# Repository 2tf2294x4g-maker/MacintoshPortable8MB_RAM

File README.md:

# Mac Portable 8MB RAM Card (v2 — All-5V)

Expands a Macintosh Portable to **9 MB total** (1 MB onboard + 8 MB this card) — the maximum the Portable's address space supports.

All-5V design using 1M×8 SRAM chips. No level shifters, no LDO regulator, no 3.3V rail. Shares the same connector, CPLD, and bus transceiver approach as the [4MB card](https://github.com/2tf2294x4g-maker/MacintoshPortable4MB_RAM) but doubles capacity using larger SRAM.

> ✅ **HARDWARE VALIDATED** — Built and tested on a Mac Portable M5120 (July 2026). Boots reliably, passes 9 MB in About This Macintosh, and with the DTACK bodge (see below) outperforms the 1 MB baseline.

---

## Photos

| | |
|---|---|
|  |  |
| System 7.5.5 — 9,216K total memory | Card seated in Portable with orange DTACK bodge wire |

*Orange bodge wire running from CPLD pin 42 to PDS slot pin B7 (/DTACK)*

| | |
|---|---|
|  |  |
| Component side — all 8 AS6C8008 SRAMs, bus transceivers, CPLD, and DTACK bodge wire | Solder side — bypass caps and bulk caps

---

## Specs

| | |
|---|---|
| Capacity | 8 MB (8× 1M×8 SRAM) |
| System total | 9 MB (1 MB onboard + 8 MB card) |
| Bus width | 8-bit × 2 banks (addressed via CPLD) |
| Logic | ATF1502ASL CPLD (5V, TQFP-44) |
| SRAM | 8× AS6C8008-55ZIN (5V, TSOP-II-44) |
| Layers | 4 (F.Cu signal / GND plane / +5V plane / B.Cu signal + pour) |
| Connector | Samtec BCS-125-F-D-HE (50-pin 2×25, horizontal entry) |
| Size jumper | JP1: OPEN = 8MB (all chips) / CLOSED = 4MB (populate U2 U3 U6 U7 only) |

---

## Bill of Materials

| Ref | Qty | Value | Package | Part / Notes |
|-----|----:|-------|---------|--------------|
| U2–U9 | 8 | AS6C8008-55ZIN | TSOP-II-44 | Alliance Memory — 1M×8 5V SRAM 55 ns |
| U1 | 1 | ATF1502ASL | TQFP-44 | Microchip ATF1502ASL-**25AU44** — must be ASL (5V), not ASV |
| U11, U12 | 2 | 74HC245 | SOIC-20 **wide** | SN74HC245**DW** — verify wide (7.5 mm) body |
| J1 | 1 | RAM connector | Samtec BCS-125-F-D-HE | 50-pin socket, horizontal entry — free Samtec sample |
| J2 | 1 | JTAG header | 1×6 2.54 mm pin header | Pin 1 (square pad) = TCK |
| JP1 | 1 | SIZE jumper | 1×2 2.54 mm pin header + shunt | OPEN=8MB, CLOSED=4MB |
| C1–C12, C17, C18 | 14 | 100 nF | 0805 | X7R 50V ceramic bypass |
| C13–C16, C19 | 5 | 10 µF | 0805 | X5R 16V ceramic bulk |
| R2–R5 | 4 | 10 KΩ | 0805 | 5% thick film |

Full BOM: [PortableRAM-8MB-BOM.csv](PortableRAM-8MB-BOM.csv)

---

## ⚠️ Important — SRAM Pinout Difference

The AS6C8008 (8MB card) and AS7C4096A (4MB card) are **both TSOP-II-44 but have different pinouts**. Do not install 4MB card SRAM chips on this board — the CE#, WE#, and OE# pins are in different locations and the board will not work correctly.

---

## Population Guide

The silkscreen shows two labeled boxes:

| Box | Chips | Config |
|-----|-------|--------|
| **4MB** | U2, U3, U6, U7 | JP1 CLOSED — populate these 4 chips only |
| **8MB ONLY** | U4, U5, U8, U9 | JP1 OPEN — populate all 8 chips |

For a full 8MB build, populate all 8 chips and leave JP1 open (no shunt).

---

## Files

```
PortableRAM-8MB.kicad_pcb     — PCB layout (KiCad 9)
PortableRAM-8MB.kicad_sch     — Schematic
PortableRAM-8MB.kicad_pro     — Project file
PortableRAM.kicad_sym         — Custom symbol library
PortableRAM.pretty/           — Custom footprint library
Gerbers/                      — Gerber + drill files (ready to order)
Gerbers.zip                   — Same, zipped (upload directly to fab)
firmware/
  PortableRAM8.pld            — CUPL source (ATF1502ASL logic)
  PortableRAM8.jed            — Compiled JEDEC
  PortableRAM8.svf            — SVF for OpenOCD programming
  program.sh                  — One-command programming script (Tigard)
  BUILD.md                    — Firmware build instructions (WinCUPL + Wine)
PortableRAM-8MB-BOM.csv
```

---

## Ordering the PCB

Upload `Gerbers.zip` to your preferred fab (JLCPCB, PCBWay, OSHPark, etc.).

**Board settings:**
- Layers: **4**
- Thickness: 1.6 mm
- Surface finish: **ENIG** (recommended — 0.8mm pitch fine-pitch pads benefit from the flat surface)
- All other settings: fab defaults

---

## Assembly Notes

Solder in this order:

1. **U1** (ATF1502ASL CPLD, TQFP-44) — centre first
2. **U2–U9** (SRAM, TSOP-II-44) — fine pitch; flux generously. See population guide above.
3. **U11, U12** (74HC245, SOIC-20 wide)
4. **C1–C18** (100 nF 0805 bypass caps)
5. **C13–C19** (10 µF 0805 bulk caps)
6. **R2–R5** (10 KΩ 0805)
7. **JP1** (1×2 header — leave open for 8MB, or install shunt for 4MB)
8. **J2** (1×6 JTAG header — before J1 for iron clearance)
9. **J1** (Samtec connector) — last

---

## Programming the CPLD

The ATF1502ASL must be programmed before the card will work. Use J2 (1×6 header on the board edge).

### J2 pinout (pin 1 = square pad)

| Pin | Signal |
|-----|--------|
| 1 | TCK |
| 2 | TMS |
| 3 | TDI |
| 4 | TDO |
| 5 | +5V |
| 6 | GND |

### With a Tigard programmer (FT2232H-based)

Set the Tigard voltage jumper to **5V** before connecting.

```bash
cd firmware
./program.sh PortableRAM8.svf
```

Success output ends with `shutdown command invoked` and no TDO mismatch errors.

See [firmware/BUILD.md](firmware/BUILD.md) for full build and programming pipeline.

---

## Installation

1. Power off and unplug the Mac Portable.
2. Remove the battery and bottom cover.
3. Seat the card on the RAM expansion header — J1 is a friction-fit horizontal-entry socket.
4. Reassemble and power on.

You should see **9 MB** in About This Macintosh.

### DTACK Performance Fix (firmware rev 12)

The Mac Portable's GLU chip generates /DTACK for the 68000 with region-dependent timing:

| Address range | GLU /DTACK | Condition |
|---|---|---|
| 0x000000–0x4FFFFF | 2 clocks | Always — hardwired fast path |
| 0x500000–0x8FFFFF | 6 clocks | Normal operation (register configured) |
| 0x500000–0x8FFFFF | 18 clocks | After sleep/wake (register reset) |

The 8 MB card spans 0x100000–0x8FFFFF, straddling the split. Banks 0–1 (0x100000–0x4FFFFF) already get the GLU's 2-clock fast path. Banks 2–3 (0x500000–0x8FFFFF) run at 6 clocks and collapse to 18 clocks after sleep/wake when the GLU's DTACK register loses its configuration.

The fix: the ATF1502ASL CPLD now asserts /DTACK itself, via a bodge wire from CPLD pin 42 to PDS slot pin B7. The CPLD monitors the address bus and data strobes, and whenever a cycle falls within the card's memory window (0x100000–0x8FFFFF) it pulls /DTACK low directly — bypassing the GLU completely. The output is tristated for all other bus cycles so there's no contention.

Because the logic is purely combinatorial (no registers, no state), it's immune to sleep/wake — the CPLD re-evaluates every cycle from scratch. The post-sleep collapse is gone.

**Benchmark results (Speedometer 3.23 / Snooper Memory Move — System 7.1, M5120):**

| Configuration | Speedometer | Snooper | Post-sleep |
|---|---|---|---|
| 1 MB card (baseline) | 1.990 | 87% | 1.985 |
| 4 MB expansion card | 1.955 | 85% | — |
| 8 MB card — no DTACK bodge | 1.486 | 51% | — |
| 8 MB card — no bodge, after sleep | 0.974 | 22% | — |
| **8 MB card + CPLD DTACK bodge** | **2.170** | **102%** | **2.170** |
| **4 MB card + CPLD DTACK bodge** | **2.170** | **102%** | **2.170** |

The CPLD's combinatorial DTACK is faster than the GLU — the 8 MB card with the bodge outperforms the 1 MB baseline. Post-sleep performance is identical to cold boot. The 4 MB configuration with the DTACK bodge also scores 102%, confirming the CPLD path is faster than even the GLU's hardwired 2-clock mode for the lower address range.

**How to wire it:** Solder a bodge wire from CPLD pin 42 (U1, TQFP-44) to PDS slot pin B7 (/DTACK). The PDS connector is the 96-pin DIN-41612 on the Mac Portable motherboard (3 rows A/B/C, 32 pins each). Pin B7 is in row B, position 7 from the component side.

---

## Cost

### PCB — JLCPCB (July 2026)

| | |
|---|---|
| 5× 4-layer boards (ENIG) | $48.70 |
| Shipping | $8.79 |
| Discount | −$5.49 |
| Tax | $3.68 |
| Payment fee | $0.52 |
| **Total for 5 boards** | **$56.20** |
| **Per board** | **~$11.24** |

ENIG finish recommended over HASL for the 0.8mm pitch TSOP-II-44 and TQFP-44 pads.

### Parts — DigiKey

| Part | Qty | Unit | Ext |
|------|----:|-----:|----:|
| ATF1502ASL-25AU44 (CPLD) | 1 | $3.12 | $3.12 |
| SN74HC245DWR (74HC245 wide SOIC) | 2 | $0.75 | $1.50 |
| 100 nF 50V X7R 0805 | 14 | $0.07 | $0.98 |
| 10 µF 16V X5R 0805 | 5 | $0.46 | $2.30 |
| 10 KΩ 5% 0805 | 4 | $0.03 | $0.12 |

### Parts — DigiKey (SRAM)

| Part | Qty | Unit | Ext |
|------|----:|-----:|----:|
| AS6C8008-55ZIN (1M×8 5V SRAM) | 10 | ~$10.17 | ~$102 |

Order 10 (8 needed + 2 spares).

### Samtec J1 Connector

Free sample from samtec.com (BCS-125-F-D-HE). Allow 1–2 weeks.

### Summary — one board from scratch

| Item | Approx cost |
|---|---|
| PCB (1 of 5 from JLCPCB, ENIG) | $11 |
| 8× AS6C8008-55ZIN SRAM | $86 |
| CPLD + transceivers + passives | $8 |
| Samtec J1 | free / ~$10 |
| **Total** | **~$105–115** |

The SRAM dominates the cost. Compared to the 4MB card (~$93–103), the extra cost is the larger SRAM chips and ENIG finish.

---

## References & Acknowledgements

This card would not exist without the following prior work:

**Dynamic Engineering Mac Portable RAM Card**
The address decode and bus control logic in `PortableRAM8.pld` is derived from the GAL22V10 PLD source files originally written for the Dynamic Engineering commercial RAM expansion card for the Mac Portable. These files define the core signal equations — bank chip-select generation, byte-lane write control via UDS*/LDS*, bus transceiver direction, and output enable timing. The original `.PLD` files were recovered and shared by *techknight* on the TinkerDifferent forum and #skunkworks Discord. Translated here from three GAL22V10 chips to a single ATF1502ASL CPLD, with corrections to the `r_w_u` equation and address decode base, and extended for 8MB capacity.

**miejas — Macintosh Portable 4MB Memory Expansion**
[https://github.com/miejas/Macintosh-Portable-4-MB-Memory-Expansion](https://github.com/miejas/Macintosh-Portable-4-MB-Memory-Expansion)
Open-source 4MB RAM card whose connector pinout, bus transceiver approach, and firmware structure were used as a cross-reference to validate signal assignments and confirm that AS* and SLEEP* are not present on the expansion connector.

**Reza Fouladian — PortableRAM BGA 8MB**
[https://github.com/rezafouladian/PortableRAM-BGA-8MB](https://github.com/rezafouladian/PortableRAM-BGA-8MB)
BGA-format 8MB card using the ATF1502ASV (3.3V CPLD) and SN74LVC4245A level translators. Used as a reference for the 8MB address decode strategy and CPLD pin planning. Reza also provided direct guidance on driving /DTACK from the CPLD and on the Mac Portable PDS connector pinout — specifically confirming that /DTACK is available on PDS pin B7 and can be driven directly from a CPLD output, which was the key insight that led to the DTACK bodge fix implemented in firmware rev 12. That fix eliminated the GLU wait-state penalty and the post-sleep performance collapse entirely.

**Apple Mac Portable Developer Notes & Schematics**
Apple's original hardware documentation for the Mac Portable expansion bus, memory map, and GLU register behaviour (including the $FC0200 DTACK register).

---

## License

- **Hardware** (schematics, PCB layout, Gerbers) — [CERN-OHL-S v2](LICENSE) · SPDX `CERN-OHL-S-2.0`
- **Firmware source** (`PortableRAM8.pld`) — [MIT](LICENSE-MIT) · SPDX `MIT`

Both licence texts are included in full in this repository.
Do what you like — just share improvements.

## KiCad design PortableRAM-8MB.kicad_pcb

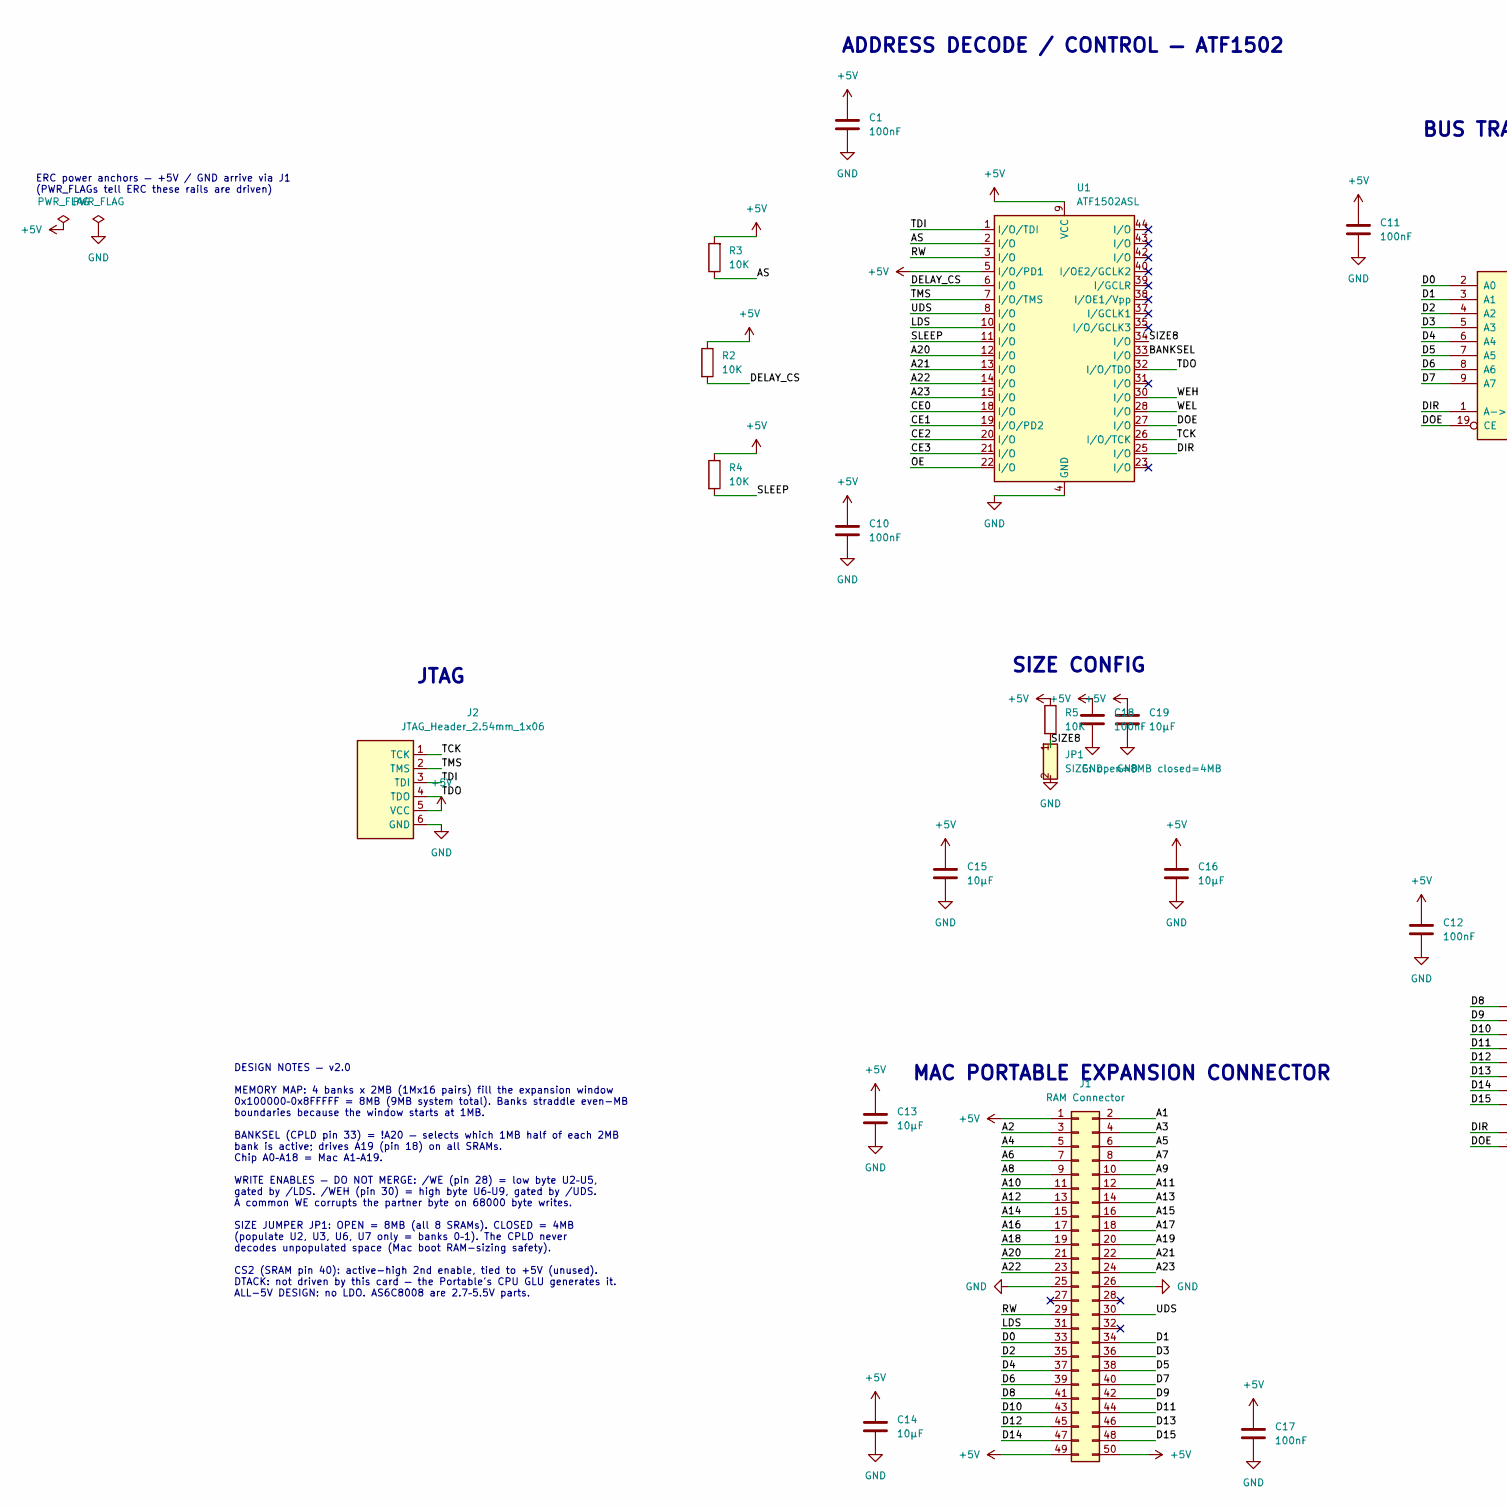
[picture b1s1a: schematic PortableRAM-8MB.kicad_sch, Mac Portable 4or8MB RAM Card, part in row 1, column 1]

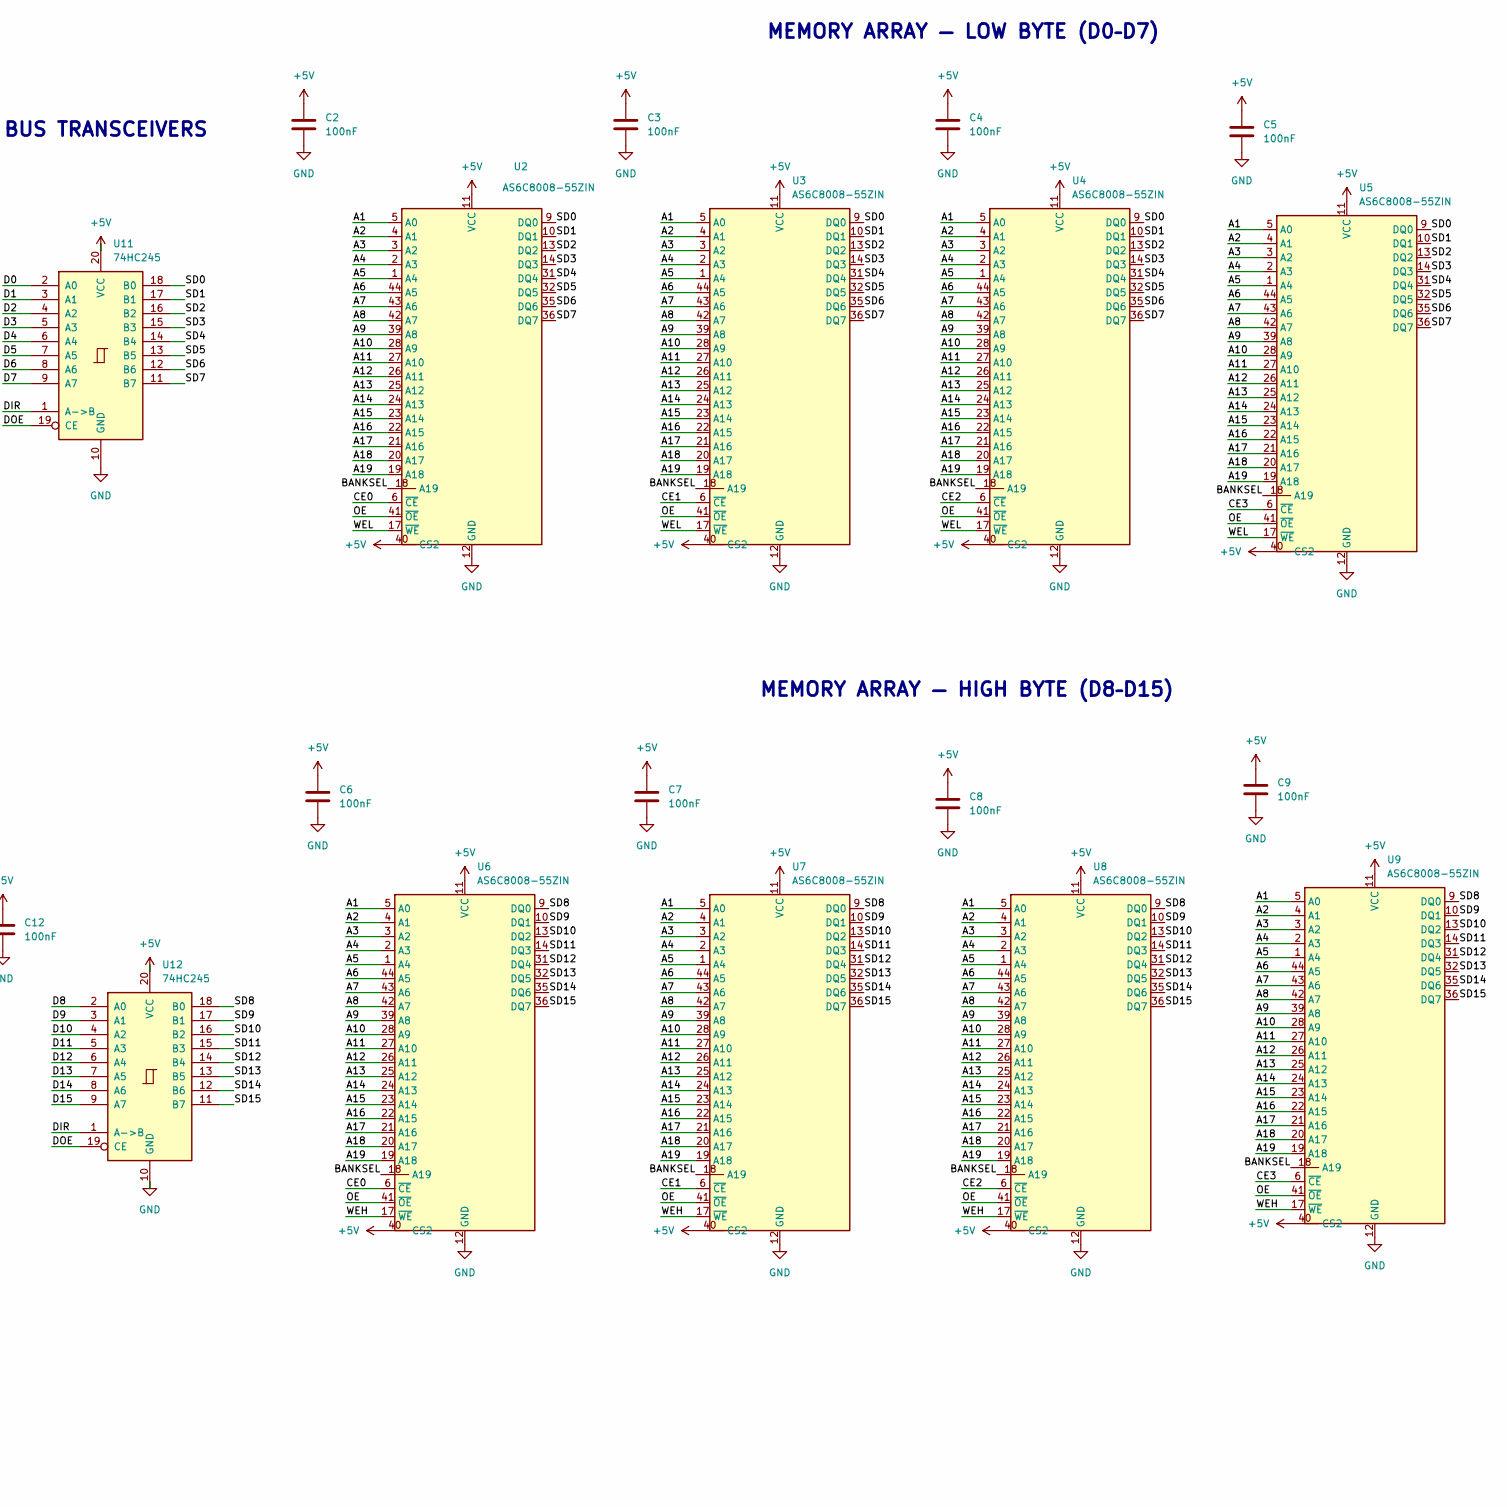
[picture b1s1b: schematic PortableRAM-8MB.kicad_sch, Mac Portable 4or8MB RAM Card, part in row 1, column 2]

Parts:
C1, C2, C3, C4, C5, C6, C7, C8, C9, C10, C11, C12, C17, C18: 100nF; C_0805_2012Metric
C13, C14, C15, C16, C19: 10µF; C_0805_2012Metric
J1: RAM Connector; Samtec_BCS-125-F-D-HE
J2: JTAG_Header_2.54mm_1x06; PinHeader_1x06_P2.54mm_Vertical
JP1: SIZE: open=8MB closed=4MB; PinHeader_1x02_P2.54mm_Vertical
R2, R3, R4, R5: 10K; R_0805_2012Metric
U1: ATF1502ASL; TQFP-44_10x10mm_P0.8mm
U2, U3, U4, U5, U6, U7, U8, U9: AS6C8008-55ZIN; TSOP-II-44_10.16x18.41mm_P0.8mm
U11, U12: 74HC245; SOIC-20W_7.5x12.8mm_P1.27mm

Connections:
+5V: C1.1, C2.1, C3.1, C4.1, C5.1, C6.1, C7.1, C8.1, C9.1, C10.1, C11.1, C12.1, C13.1, C14.1, C15.1, C16.1, C17.1, C18.1, C19.1, J1.1, J1.49, J1.50, J2.5 (VCC), R2.1, R3.2, R4.1, R5.1, U1.5 (I/O/PD1), U1.9 (VCC), U1.17 (VCC), U1.29 (VCC), U1.41 (VCC), U2.11 (VCC), U2.33 (VCC), U2.40 (CS2), U3.11 (VCC), U3.33 (VCC), U3.40 (CS2), U4.11 (VCC), U4.33 (VCC), U4.40 (CS2), U5.11 (VCC), U5.33 (VCC), U5.40 (CS2), U6.11 (VCC), U6.33 (VCC), U6.40 (CS2), U7.11 (VCC), U7.33 (VCC), U7.40 (CS2), U8.11 (VCC), U8.33 (VCC), U8.40 (CS2), U9.11 (VCC), U9.33 (VCC), U9.40 (CS2), U11.20 (VCC), U12.20 (VCC)
/A1: J1.2, U2.5 (A0), U3.5 (A0), U4.5 (A0), U5.5 (A0), U6.5 (A0), U7.5 (A0), U8.5 (A0), U9.5 (A0)
/A2: J1.3, U2.4 (A1), U3.4 (A1), U4.4 (A1), U5.4 (A1), U6.4 (A1), U7.4 (A1), U8.4 (A1), U9.4 (A1)
/A3: J1.4, U2.3 (A2), U3.3 (A2), U4.3 (A2), U5.3 (A2), U6.3 (A2), U7.3 (A2), U8.3 (A2), U9.3 (A2)
/A4: J1.5, U2.2 (A3), U3.2 (A3), U4.2 (A3), U5.2 (A3), U6.2 (A3), U7.2 (A3), U8.2 (A3), U9.2 (A3)
/A5: J1.6, U2.1 (A4), U3.1 (A4), U4.1 (A4), U5.1 (A4), U6.1 (A4), U7.1 (A4), U8.1 (A4), U9.1 (A4)
/A6: J1.7, U2.44 (A5), U3.44 (A5), U4.44 (A5), U5.44 (A5), U6.44 (A5), U7.44 (A5), U8.44 (A5), U9.44 (A5)
/A7: J1.8, U2.43 (A6), U3.43 (A6), U4.43 (A6), U5.43 (A6), U6.43 (A6), U7.43 (A6), U8.43 (A6), U9.43 (A6)
/A8: J1.9, U2.42 (A7), U3.42 (A7), U4.42 (A7), U5.42 (A7), U6.42 (A7), U7.42 (A7), U8.42 (A7), U9.42 (A7)
/A9: J1.10, U2.39 (A8), U3.39 (A8), U4.39 (A8), U5.39 (A8), U6.39 (A8), U7.39 (A8), U8.39 (A8), U9.39 (A8)
/A10: J1.11, U2.28 (A9), U3.28 (A9), U4.28 (A9), U5.28 (A9), U6.28 (A9), U7.28 (A9), U8.28 (A9), U9.28 (A9)
/A11: J1.12, U2.27 (A10), U3.27 (A10), U4.27 (A10), U5.27 (A10), U6.27 (A10), U7.27 (A10), U8.27 (A10), U9.27 (A10)
/A12: J1.13, U2.26 (A11), U3.26 (A11), U4.26 (A11), U5.26 (A11), U6.26 (A11), U7.26 (A11), U8.26 (A11), U9.26 (A11)
/A13: J1.14, U2.25 (A12), U3.25 (A12), U4.25 (A12), U5.25 (A12), U6.25 (A12), U7.25 (A12), U8.25 (A12), U9.25 (A12)
/A14: J1.15, U2.24 (A13), U3.24 (A13), U4.24 (A13), U5.24 (A13), U6.24 (A13), U7.24 (A13), U8.24 (A13), U9.24 (A13)
/A15: J1.16, U2.23 (A14), U3.23 (A14), U4.23 (A14), U5.23 (A14), U6.23 (A14), U7.23 (A14), U8.23 (A14), U9.23 (A14)
/A16: J1.17, U2.22 (A15), U3.22 (A15), U4.22 (A15), U5.22 (A15), U6.22 (A15), U7.22 (A15), U8.22 (A15), U9.22 (A15)
/A17: J1.18, U2.21 (A16), U3.21 (A16), U4.21 (A16), U5.21 (A16), U6.21 (A16), U7.21 (A16), U8.21 (A16), U9.21 (A16)
/A18: J1.19, U2.20 (A17), U3.20 (A17), U4.20 (A17), U5.20 (A17), U6.20 (A17), U7.20 (A17), U8.20 (A17), U9.20 (A17)
/A19: J1.20, U2.19 (A18), U3.19 (A18), U4.19 (A18), U5.19 (A18), U6.19 (A18), U7.19 (A18), U8.19 (A18), U9.19 (A18)
/A20: J1.21, U1.12 (I/O)
/A21: J1.22, U1.13 (I/O)
/A22: J1.23, U1.14 (I/O)
/A23: J1.24, U1.15 (I/O)
/AS: R3.1, U1.2 (I/O)
/BANKSEL: U1.33 (I/O), U2.18 (A19), U3.18 (A19), U4.18 (A19), U5.18 (A19), U6.18 (A19), U7.18 (A19), U8.18 (A19), U9.18 (A19)
/CE0: U1.18 (I/O), U2.6 (~CE), U6.6 (~CE)
/CE1: U1.19 (I/O/PD2), U3.6 (~CE), U7.6 (~CE)
/CE2: U1.20 (I/O), U4.6 (~CE), U8.6 (~CE)
/CE3: U1.21 (I/O), U5.6 (~CE), U9.6 (~CE)
/D0: J1.33, U11.2 (A0)
/D1: J1.34, U11.3 (A1)
/D2: J1.35, U11.4 (A2)
/D3: J1.36, U11.5 (A3)
/D4: J1.37, U11.6 (A4)
/D5: J1.38, U11.7 (A5)
/D6: J1.39, U11.8 (A6)
/D7: J1.40, U11.9 (A7)
/D8: J1.41, U12.2 (A0)
/D9: J1.42, U12.3 (A1)
/D10: J1.43, U12.4 (A2)
/D11: J1.44, U12.5 (A3)
/D12: J1.45, U12.6 (A4)
/D13: J1.46, U12.7 (A5)
/D14: J1.47, U12.8 (A6)
/D15: J1.48, U12.9 (A7)
/DELAY_CS: R2.2, U1.6 (I/O)
/DIR: U1.25 (I/O), U11.1 (A->B), U12.1 (A->B)
/DOE: U1.27 (I/O), U11.19 (CE), U12.19 (CE)
/LDS: J1.31, U1.10 (I/O)
/OE: U1.22 (I/O), U2.41 (~OE), U3.41 (~OE), U4.41 (~OE), U5.41 (~OE), U6.41 (~OE), U7.41 (~OE), U8.41 (~OE), U9.41 (~OE)
/RW: J1.29, U1.3 (I/O)
/SD0: U2.9 (DQ0), U3.9 (DQ0), U4.9 (DQ0), U5.9 (DQ0), U11.18 (B0)
/SD1: U2.10 (DQ1), U3.10 (DQ1), U4.10 (DQ1), U5.10 (DQ1), U11.17 (B1)
/SD2: U2.13 (DQ2), U3.13 (DQ2), U4.13 (DQ2), U5.13 (DQ2), U11.16 (B2)
/SD3: U2.14 (DQ3), U3.14 (DQ3), U4.14 (DQ3), U5.14 (DQ3), U11.15 (B3)
/SD4: U2.31 (DQ4), U3.31 (DQ4), U4.31 (DQ4), U5.31 (DQ4), U11.14 (B4)
/SD5: U2.32 (DQ5), U3.32 (DQ5), U4.32 (DQ5), U5.32 (DQ5), U11.13 (B5)
/SD6: U2.35 (DQ6), U3.35 (DQ6), U4.35 (DQ6), U5.35 (DQ6), U11.12 (B6)
/SD7: U2.36 (DQ7), U3.36 (DQ7), U4.36 (DQ7), U5.36 (DQ7), U11.11 (B7)
/SD8: U6.9 (DQ0), U7.9 (DQ0), U8.9 (DQ0), U9.9 (DQ0), U12.18 (B0)
/SD9: U6.10 (DQ1), U7.10 (DQ1), U8.10 (DQ1), U9.10 (DQ1), U12.17 (B1)
/SD10: U6.13 (DQ2), U7.13 (DQ2), U8.13 (DQ2), U9.13 (DQ2), U12.16 (B2)
/SD11: U6.14 (DQ3), U7.14 (DQ3), U8.14 (DQ3), U9.14 (DQ3), U12.15 (B3)
/SD12: U6.31 (DQ4), U7.31 (DQ4), U8.31 (DQ4), U9.31 (DQ4), U12.14 (B4)
/SD13: U6.32 (DQ5), U7.32 (DQ5), U8.32 (DQ5), U9.32 (DQ5), U12.13 (B5)
/SD14: U6.35 (DQ6), U7.35 (DQ6), U8.35 (DQ6), U9.35 (DQ6), U12.12 (B6)
/SD15: U6.36 (DQ7), U7.36 (DQ7), U8.36 (DQ7), U9.36 (DQ7), U12.11 (B7)
/SIZE8: JP1.1, R5.2, U1.34 (I/O)
/SLEEP: R4.2, U1.11 (I/O)
/TCK: J2.1 (TCK), U1.26 (I/O/TCK)
/TDI: J2.3 (TDI), U1.1 (I/O/TDI)
/TDO: J2.4 (TDO), U1.32 (I/O/TDO)
/TMS: J2.2 (TMS), U1.7 (I/O/TMS)
/UDS: J1.30, U1.8 (I/O)
/WEH: U1.30 (I/O), U6.17 (~WE), U7.17 (~WE), U8.17 (~WE), U9.17 (~WE)
/WEL: U1.28 (I/O), U2.17 (~WE), U3.17 (~WE), U4.17 (~WE), U5.17 (~WE)
GND: C1.2, C2.2, C3.2, C4.2, C5.2, C6.2, C7.2, C8.2, C9.2, C10.2, C11.2, C12.2, C13.2, C14.2, C15.2, C16.2, C17.2, C18.2, C19.2, J1.25, J1.26, J2.6 (GND), JP1.2, U1.4 (GND), U1.16 (GND), U1.24 (GND), U1.36 (GND), U2.12 (GND), U2.34 (GND), U3.12 (GND), U3.34 (GND), U4.12 (GND), U4.34 (GND), U5.12 (GND), U5.34 (GND), U6.12 (GND), U6.34 (GND), U7.12 (GND), U7.34 (GND), U8.12 (GND), U8.34 (GND), U9.12 (GND), U9.34 (GND), U11.10 (GND), U12.10 (GND); also elsewhere on the board

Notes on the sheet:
ERC power anchors — +5V / GND arrive via J1 (PWR_FLAGs tell ERC these rails are driven)
JTAG
MAC PORTABLE EXPANSION CONNECTOR
ADDRESS DECODE / CONTROL — ATF1502
BUS TRANSCEIVERS
MEMORY ARRAY — LOW BYTE (D0–D7)
DESIGN NOTES — v2.0 MEMORY MAP: 4 banks x 2MB (1Mx16 pairs) fill the expansion window 0x100000–0x8FFFFF = 8MB (9MB system total). Banks straddle even-MB boundaries because the window starts at 1MB. BANKSEL (CPLD pin 33) = !A20 — selects which 1MB half of each 2MB bank is active; drives A19 (pin 18)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
MEMORY ARRAY — HIGH BYTE (D8–D15)
SIZE CONFIG

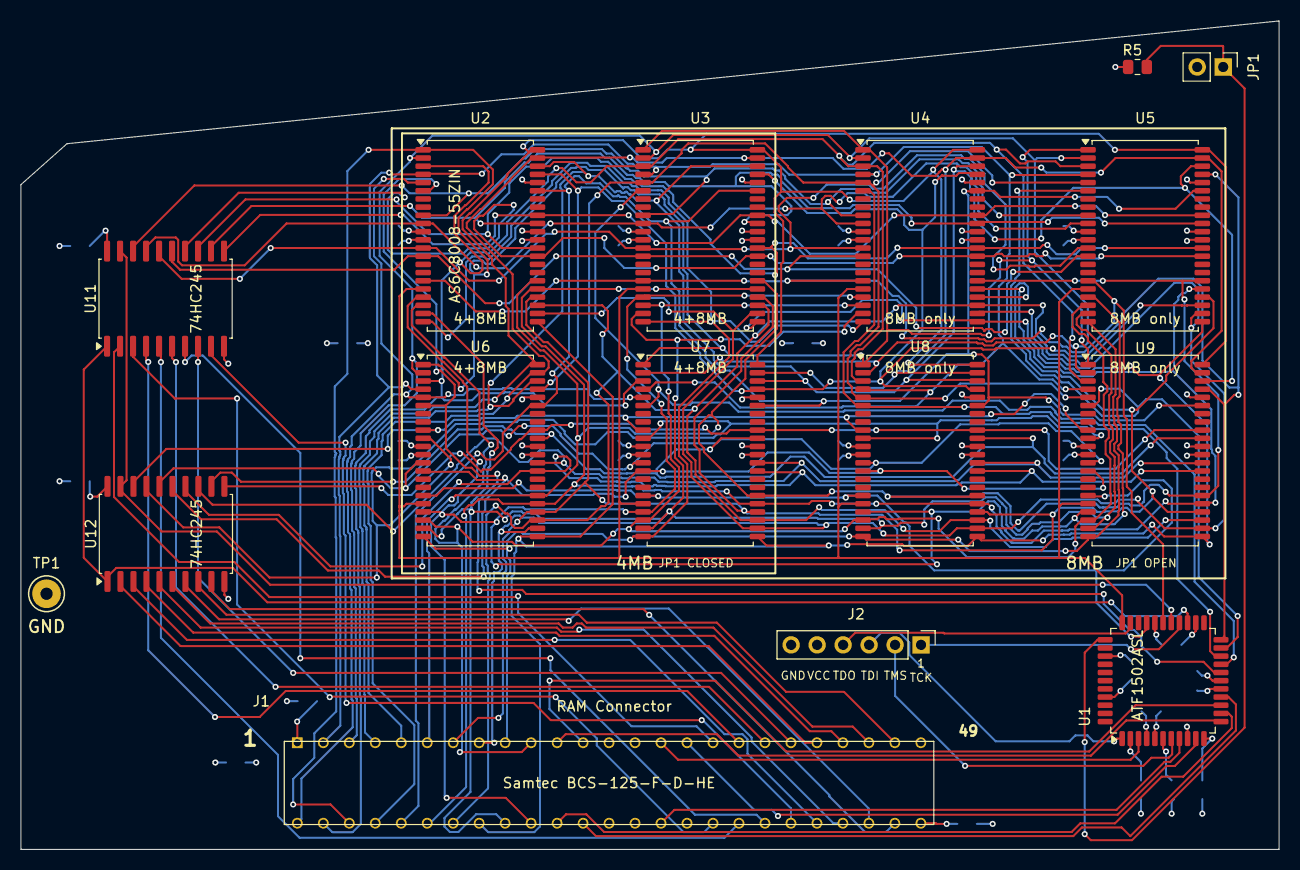
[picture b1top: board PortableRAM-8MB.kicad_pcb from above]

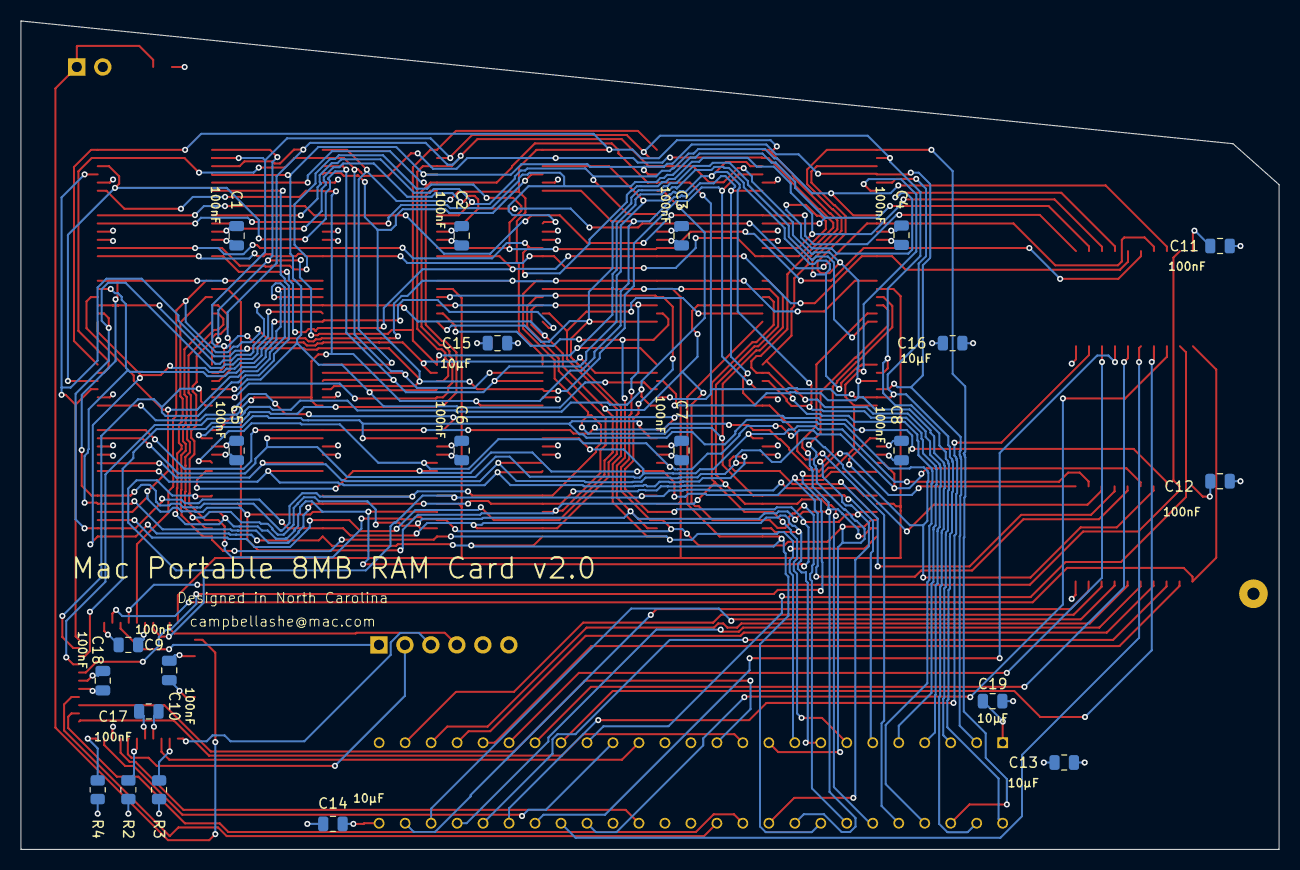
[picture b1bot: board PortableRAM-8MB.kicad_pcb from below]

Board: 4 copper layers, 123.0 x 81.0 mm, 38 parts (22 on the bottom side), 78 nets.

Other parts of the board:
TP1: GND; TestPoint_GND

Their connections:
GND: TP1.1; also elsewhere on the board

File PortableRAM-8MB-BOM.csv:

Ref,Qty,Value,Package,Manufacturer,Mfr Part Number,Notes
U2-U9,8,AS6C8008-55ZIN,TSOP-II-44 (10.16x18.41mm P0.8mm),Alliance Memory,AS6C8008-55ZIN,1Mx8 SRAM 5V 55ns (Z=TSOP-II pkg); ~$13-15 each; order 1-2 spares; 8 chips = 8MB
U1,1,ATF1502ASL,TQFP-44 (10x10mm P0.8mm),Microchip,ATF1502ASL-25AU44,5V CPLD (ASL = 5V; do NOT order ASV which is 3.3V); needs JTAG programming; order a spare
U11 U12,2,74HC245,SOIC-20W (7.5mm wide),TI/Nexperia,SN74HC245DW,Octal bus transceiver 5V; verify WIDE SOIC-20 body (DW/DWR suffix)
J1,1,RAM Connector,Samtec BCS-125-F-D-HE,Samtec,BCS-125-F-D-HE,50-pin 2x25 2.54mm socket strip; footprint verified vs drawing
J2,1,JTAG Header 1x06,PinHeader 2.54mm 1x06 vertical,Generic,,Standard 0.1in header for CPLD JTAG programming
JP1,1,SIZE jumper 1x02,PinHeader 2.54mm 1x02 vertical,Generic,,Size select: OPEN=8MB (all 8 SRAMs) / CLOSED=4MB (populate U2 U3 U6 U7 only). Add one 2.54mm shunt.
C1-C12 C17 C18,14,100nF,0805 (2012 metric),Generic,,X7R 50V ceramic; one per chip + per CPLD VCC pin; buy strip of 50+
C13-C16 C19,5,10uF,0805 (2012 metric),Generic,,X5R 16V ceramic bulk; C19 at J1 power entry; buy 10+
R2-R5,4,10K,0805 (2012 metric),Generic,,5% thick film pull-ups (R5 = SIZE8 jumper pull-up to +5V); buy strip
